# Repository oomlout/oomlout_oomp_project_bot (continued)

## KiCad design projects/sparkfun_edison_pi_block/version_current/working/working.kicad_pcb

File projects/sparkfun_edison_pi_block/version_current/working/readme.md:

# OOMP Project  
## Edison_Pi_Block  by sparkfun  
  
oomp key: oomp_projects_flat_sparkfun_edison_pi_block  
(snippet of original readme)  
  
SparkFun Edison Pi Block  
========================  

[*SparkFun Edison Pi Block (DEV-13044)*](https://www.sparkfun.com/products/13044)  
  
The Pi Block is a simple breakout board to bring the GPIO from the Intel Edison to the user. The Block provides level-shifted access to basic GPIO, PWM, UART, I<sup>2</sup>C, and SPI. The pins are presented in the same configuration as a [Raspberry Pi Model B header](http://elinux.org/RPi_Low-level_peripherals-Model_A_and_B_.28Original.29).  
  
Access to the GPIO pins can be accomplished through [MRAA](https://github.com/intel-iot-devkit/mraa). The GPIO number listed on the board or Linux is not the same as MRAA. Refer to the table to see which GPIO pin maps to which number in MRAA.   
  
*MRAA pin map table based on [Intel's IOT Dev Kit Repository](https://github.com/intel-iot-devkit/mraa/blob/master/docs/edison.md)*  
  
*Pins on the Pi Block are denoted with a * after the GP number*  
  
<table class="table table-bordered">  
<thead><tr><th class="text-center" title="Field -1">Edison Pin (Linux)</th>  
<th class="text-center" title="Field -2">Arduino Breakout</th>  
<th class="text-center" title="Field -3">Mini Breakout</th>  
<th class="text-center" title="Field -4">MRAA Number</th>  
<th class="text-center" title="Field -5">Pinmode0</th>  
<th class="text-center" title="Field -6">Pinmode1</th>  
<th class="text-center" title="Field -7">Pinmode2</th>  
</tr></thead>  
<tbody><tr cla  
  full source readme at [readme_src.md](readme_src.md)  
  
source repo at: [https://github.com/sparkfun/Edison_Pi_Block](https://github.com/sparkfun/Edison_Pi_Block)  
## Board  

## Schematic  

[schematic pdf](working_schematic.pdf)  
## Images

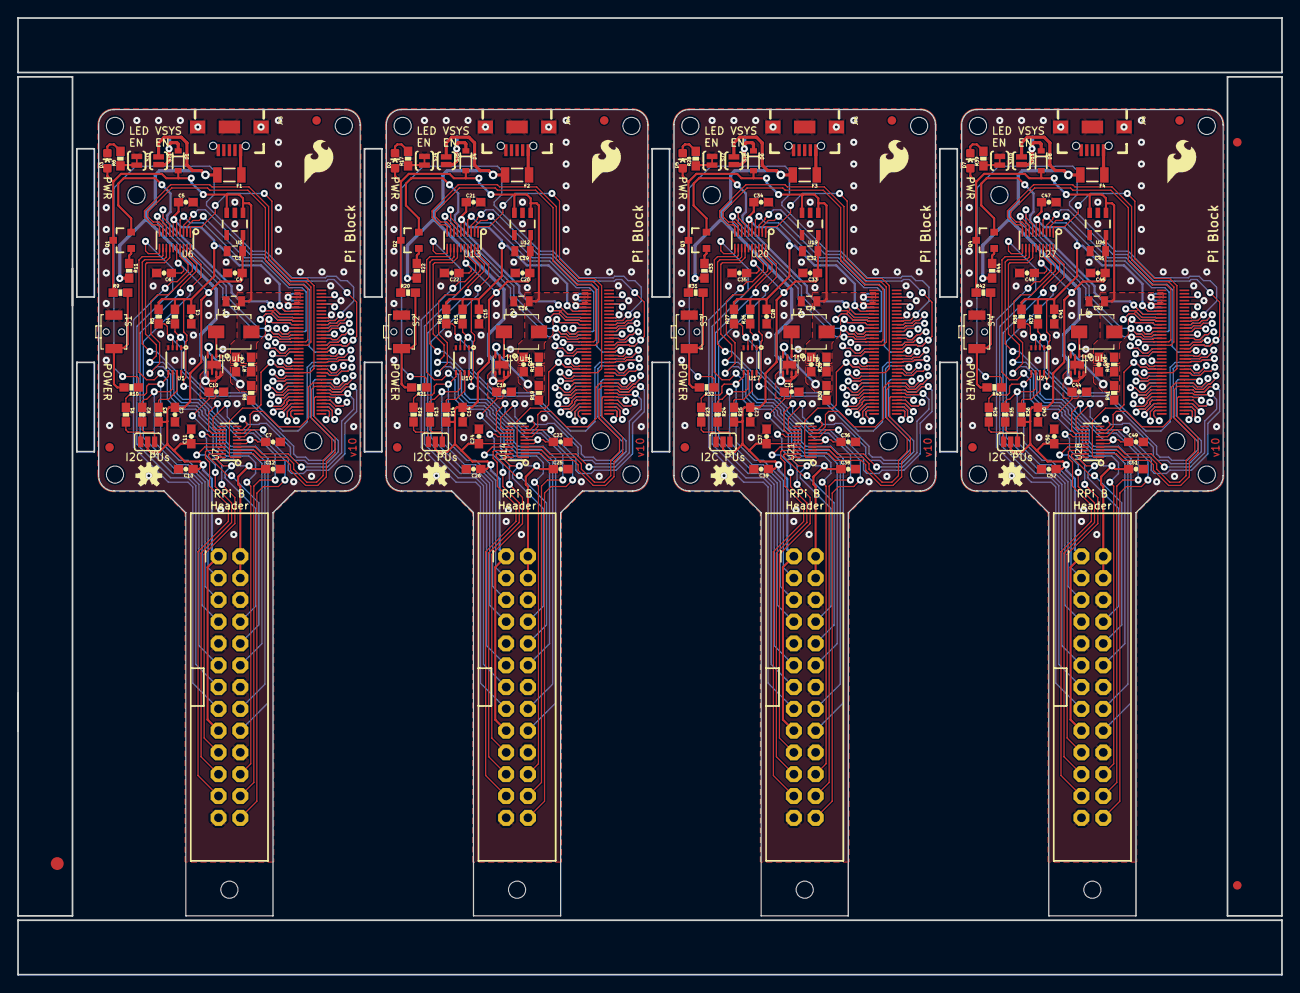
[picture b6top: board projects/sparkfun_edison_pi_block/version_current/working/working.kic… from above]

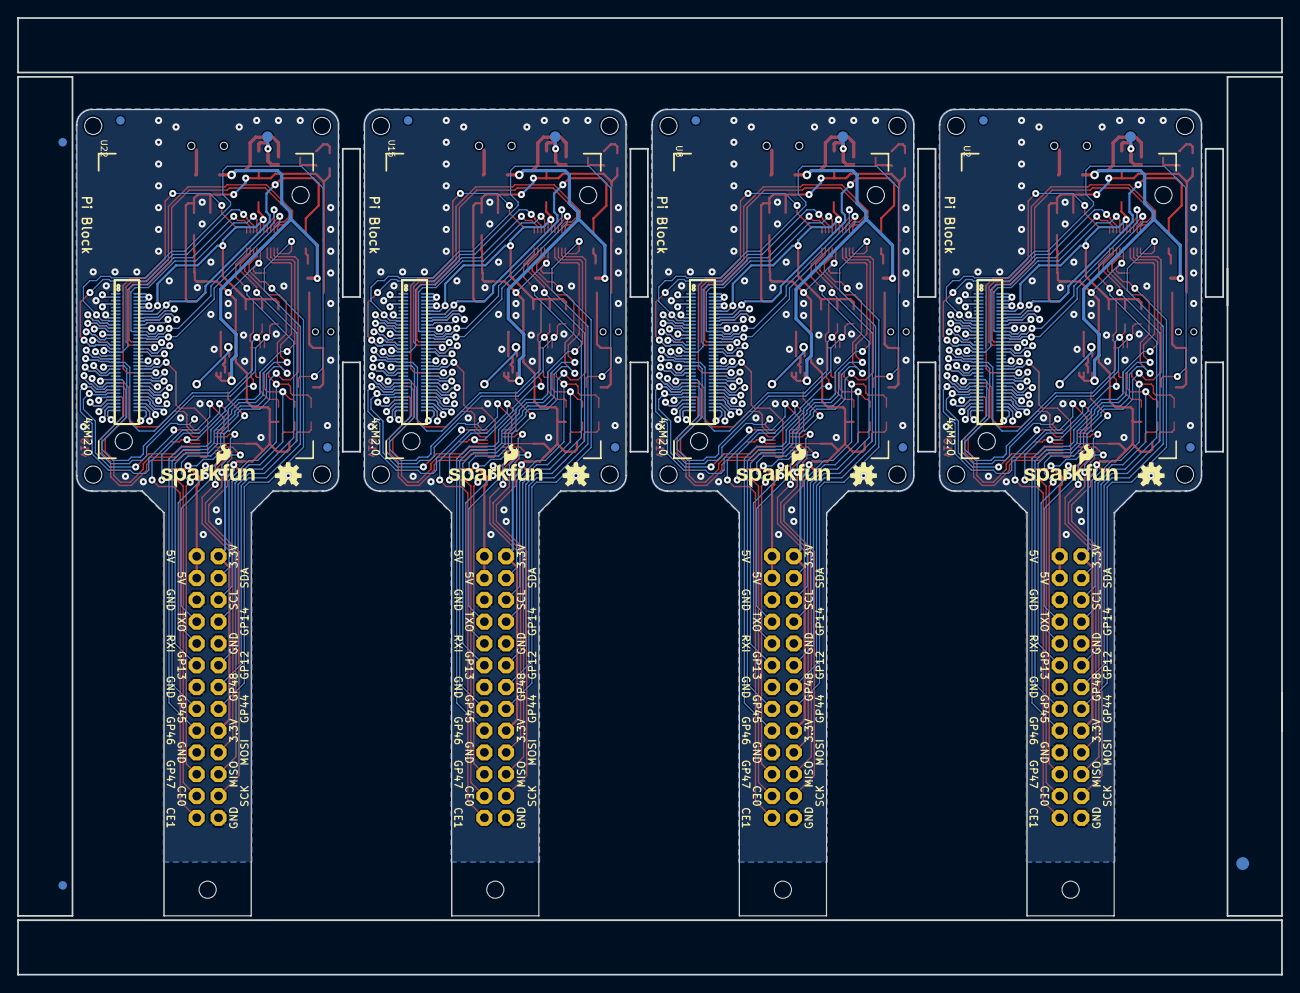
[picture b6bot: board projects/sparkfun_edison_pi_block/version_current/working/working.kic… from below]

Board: 4 copper layers, 147.3 x 111.5 mm, 230 parts (31 on the bottom side), 352 nets.

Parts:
@HOLE0, @HOLE1, @HOLE2, @HOLE3, @HOLE4, @HOLE5, @HOLE6, @HOLE7, @HOLE8, @HOLE9, @HOLE10, @HOLE11, @HOLE12, @HOLE13, @HOLE14, @HOLE15, @HOLE16, @HOLE17, @HOLE18, @HOLE19: (no value)
C1, C2, C4, C5, C6, C7, C11, C14, C15, C20, C21, C22, C23, C24, C27, C28, C33, C34, C35, C36, C37, C40, C41, C46, C47, C48, C49, C50: 0.1uF; 0603-CAP
C3, C19, C32, C45: 10uF; 0805
C8, C16, C29, C42: 22uF; 0805
C9, C17, C30, C43: 9.0pF; 0603-CAP
C10, C18, C31, C44: 4.7uF; 0603-CAP
C12, C13, C25, C26, C38, C39, C51, C52: 1.0uF; 0603-CAP
D1, D4, D6, D8: BAT20J; SOD-323
D2, D3, D5, D7: BLUE; LED-0603
E$1, E$2: FIDUCIAL-1.5X3
E$3, E$4, E$5, E$6: FIDUCIAL-1X2
F1, F2, F3, F4: PTCSMD; PTC-1206
FID1, FID2, FID3, FID4, FID5, FID6, FID7, FID8, FID9, FID10, FID11, FID12, FID13, FID14, FID15, FID16: FIDUCIAL1X2; FIDUCIAL-1X2
JP1, JP2, JP5, JP7: RASPBERRYPI-GPIOPTH; 2X13-SHROUDED
JP3, JP4, JP6, JP8: USB_MICROB; USB-B-MICRO-SMD_V03
L1, L2, L3, L4: 1.0uH; INDUCTOR-SRP4020
LOGO1, LOGO2, LOGO5, LOGO6, LOGO9, LOGO10, LOGO13, LOGO14: OSHW-LOGOS; OSHW-LOGO-S
LOGO3, LOGO8, LOGO12, LOGO16: SFE_LOGO_FLAME.2_INCH; SFE_LOGO_FLAME_.2
LOGO4, LOGO7, LOGO11, LOGO15: SFE_LOGO_NAME_FLAME.1_INCH; SFE_LOGO_NAME_FLAME_.1
Q1, Q2, Q3, Q4: 200mA/50V; SOT23-3
R1, R2, R9, R12, R13, R20, R23, R24, R31, R34, R35, R42: 10K; 0603-RES
R3, R14, R25, R36: 200k; 0603-RES
R4, R5, R15, R16, R26, R27, R37, R38: DNP; 0603-RES
R6, R11, R17, R22, R28, R33, R39, R44: 1K; 0603-RES
R7, R18, R29, R40: 680k; 0603-RES
R8, R19, R30, R41: 120k; 0603-RES
R10, R21, R32, R43: 220; 0603-RES
S1, S2, S3, S4: POWER; TACTILE_SWITCH-SMD-RIGHT-ANGLE
SJ1, SJ5, SJ8, SJ11: JUMPER-PAD-2-NOYES_SILK; PAD-JUMPER-2-NO_YES_SILK
SJ2, SJ6, SJ9, SJ12: JUMPER-PAD-3-NC_BY_PASTE; PAD-JUMPER-3-NC_BY_PASTE_YES_SILK_FULL_BOX
SJ3, SJ4, SJ7, SJ10: JUMPER-PAD-2-NC_BY_TRACE; PAD-JUMPER-2-NC_BY_TRACE_YES_SILK
TP1, TP2, TP3, TP4: TEST-POINT3X5; PAD.03X.05
U1, U10, U17, U24: PCA9306; PCA9306DC-1_1
U2, U8, U15, U22: EDISON_CONNECTOR_FULLMOUNTING_HOLES; EDISON_DAUGHTER
U3, U9, U16, U23: EDISON_CONNECTOR_FULLHEADER; DF40C-70DP-0.4(51)
U4, U11, U18, U25: TPS62065; WSON-8-PAD
U5, U12, U19, U26: MIC5219 3.3V; SOT23-5
U6, U7, U13, U14, U20, U21, U27, U28: TXB0108; UFDFN-20

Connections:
1.8V: C1.1, C5.1, C7.1, R4.2, R5.2, U1.1, U2.12, U3.12, U6.5, U6.6, U7.5, U7.6
1.8V1: C15.1, C21.1, C23.1, R15.2, R16.2, U8.12, U9.12, U10.1, U13.5, U13.6, U14.5, U14.6
1.8V2: C28.1, C34.1, C36.1, R26.2, R27.2, U15.12, U16.12, U17.1, U20.5, U20.6, U21.5, U21.6
1.8V3: C41.1, C47.1, C49.1, R37.2, R38.2, U22.12, U23.12, U24.1, U27.5, U27.6, U28.5, U28.6
3.3V: U2.8, U2.10, U3.8, U3.10
3.3V1: U8.8, U8.10, U9.8, U9.10
3.3V2: U15.8, U15.10, U16.8, U16.10
3.3V3: U22.8, U22.10, U23.8, U23.10
3.3V_LOCAL: C2.1, C3.1, C4.1, C6.1, C11.1, C13.1, JP1.1, JP1.17, R3.2, SJ2.2, U5.5, U6.16, U7.16
3.3V_LOCAL1: C14.1, C19.1, C20.1, C22.1, C24.1, C26.1, JP2.1, JP2.17, R14.2, SJ6.2, U12.5, U13.16, U14.16
3.3V_LOCAL2: C27.1, C32.1, C33.1, C35.1, C37.1, C39.1, JP5.1, JP5.17, R25.2, SJ9.2, U19.5, U20.16, U21.16
3.3V_LOCAL3: C40.1, C45.1, C46.1, C48.1, C50.1, C52.1, JP7.1, JP7.17, R36.2, SJ12.2, U26.5, U27.16, U28.16
5V: C10.1, C12.1, F1.2, JP1.2, JP1.4, R11.2, SJ1.1, U4.5, U4.7, U4.8
5V1: C18.1, C25.1, F2.2, JP2.2, JP2.4, R22.2, SJ5.1, U11.5, U11.7, U11.8
5V2: C31.1, C38.1, F3.2, JP5.2, JP5.4, R33.2, SJ8.1, U18.5, U18.7, U18.8
5V3: C44.1, C51.1, F4.2, JP7.2, JP7.4, R44.2, SJ11.1, U25.5, U25.7, U25.8
DCIN: Q1.2, U2.14, U3.14
DCIN1: Q2.2, U8.14, U9.14
DCIN2: Q3.2, U15.14, U16.14
DCIN3: Q4.2, U22.14, U23.14
FAULT: U2.19, U3.19
FAULT1: U8.19, U9.19
FAULT2: U15.19, U16.19
FAULT3: U22.19, U23.19
FW_RCVR: U2.69, U3.69
FW_RCVR1: U8.69, U9.69
FW_RCVR2: U15.69, U16.69
FW_RCVR3: U22.69, U23.69
GND: C1.2, C2.2, C3.2, C4.2, C5.2, C6.2, C7.2, C8.2, C10.2, C11.2, C12.2, C13.2, JP1.6, JP1.9, JP1.14, JP1.20, JP1.25, JP3.GND1, JP3.SHIELD1, JP3.SHIELD2, JP3.SHIELD3, R8.1, S1.1, SJ3.1, U1.4, U2.1, U2.5, U2.9, U2.11, U2.13, U2.15, U3.1, U3.5, U3.9, U3.11, U3.13, U3.15, U4.1, U4.3, U4.6, U4.PAD, U5.2, U6.15, U7.15
GND1: C14.2, C15.2, C16.2, C18.2, C19.2, C20.2, C21.2, C22.2, C23.2, C24.2, C25.2, C26.2, JP2.6, JP2.9, JP2.14, JP2.20, JP2.25, JP4.GND1, JP4.SHIELD1, JP4.SHIELD2, JP4.SHIELD3, R19.1, S2.1, SJ4.1, U8.1, U8.5, U8.9, U8.11, U8.13, U8.15, U9.1, U9.5, U9.9, U9.11, U9.13, U9.15, U10.4, U11.1, U11.3, U11.6, U11.PAD, U12.2, U13.15, U14.15
GND2: C27.2, C28.2, C29.2, C31.2, C32.2, C33.2, C34.2, C35.2, C36.2, C37.2, C38.2, C39.2, JP5.6, JP5.9, JP5.14, JP5.20, JP5.25, JP6.GND1, JP6.SHIELD1, JP6.SHIELD2, JP6.SHIELD3, R30.1, S3.1, SJ7.1, U15.1, U15.5, U15.9, U15.11, U15.13, U15.15, U16.1, U16.5, U16.9, U16.11, U16.13, U16.15, U17.4, U18.1, U18.3, U18.6, U18.PAD, U19.2, U20.15, U21.15
GND3: C40.2, C41.2, C42.2, C44.2, C45.2, C46.2, C47.2, C48.2, C49.2, C50.2, C51.2, C52.2, JP7.6, JP7.9, JP7.14, JP7.20, JP7.25, JP8.GND1, JP8.SHIELD1, JP8.SHIELD2, JP8.SHIELD3, R41.1, S4.1, SJ10.1, U22.1, U22.5, U22.9, U22.11, U22.13, U22.15, U23.1, U23.5, U23.9, U23.11, U23.13, U23.15, U24.4, U25.1, U25.3, U25.6, U25.PAD, U26.2, U27.15, U28.15
GP1: U8.48, U9.48, U13.1
GP2: U8.42, U9.42
GP3: U8.34, U9.34
GP4: U8.32, U9.32, U13.10
GP5: U8.30, U9.30, U13.9
GP6: U8.28, U9.28, U13.8
GP7: U8.26, U9.26, U13.7
GP8: U8.25, U9.25
GP9: U8.24, U9.24, U13.4
GP10: U15.48, U16.48, U20.1
GP11: U15.42, U16.42
GP12: U15.34, U16.34
GP12_PWM0: U2.35, U3.35, U6.2
GP12_PWM1: U8.35, U9.35, U13.2
GP12_PWM2: U15.35, U16.35, U20.2
GP12_PWM3: U22.35, U23.35, U27.2
GP13: U15.32, U16.32, U20.10
GP13_PWM1: U2.33, U3.33, U6.3
GP13_PWM2: U8.33, U9.33, U13.3
GP13_PWM3: U15.33, U16.33, U20.3
GP13_PWM4: U22.33, U23.33, U27.3
GP14: U2.48, U3.48, U6.1
GP15: U2.42, U3.42
GP16: U15.30, U16.30, U20.9
GP17: U15.28, U16.28, U20.8
GP18: U15.26, U16.26, U20.7
GP19: U15.25, U16.25
GP19_I2C_1_SCL: R4.1, U1.2, U2.41, U3.41
GP19_I2C_1_SCL1: R15.1, U8.41, U9.41, U10.2
GP19_I2C_1_SCL2: R26.1, U15.41, U16.41, U17.2
GP19_I2C_1_SCL3: R37.1, U22.41, U23.41, U24.2
GP20: U15.24, U16.24, U20.4
GP20_I2C_1_SDA: R5.1, U1.3, U2.43, U3.43
GP20_I2C_1_SDA1: R16.1, U8.43, U9.43, U10.3
GP20_I2C_1_SDA2: R27.1, U15.43, U16.43, U17.3
GP20_I2C_1_SDA3: R38.1, U22.43, U23.43, U24.3
GP21: U22.48, U23.48, U27.1
GP22: U22.42, U23.42
GP23: U22.34, U23.34
GP24: U22.32, U23.32, U27.10
GP25: U22.30, U23.30, U27.9
GP26: U22.28, U23.28, U27.8
GP27: U22.26, U23.26, U27.7
GP27_I2C_6_SCL: U2.45, U3.45
GP27_I2C_6_SCL1: U8.45, U9.45
GP27_I2C_6_SCL2: U15.45, U16.45
GP27_I2C_6_SCL3: U22.45, U23.45
GP28: U22.25, U23.25
GP28_I2C_6_SDA: U2.47, U3.47
GP28_I2C_6_SDA1: U8.47, U9.47
GP28_I2C_6_SDA2: U15.47, U16.47
GP28_I2C_6_SDA3: U22.47, U23.47
GP29: U22.24, U23.24, U27.4
GP40_I2S_2_CLK: U2.52, U3.52
GP40_I2S_2_CLK1: U8.52, U9.52
GP40_I2S_2_CLK2: U15.52, U16.52
GP40_I2S_2_CLK3: U22.52, U23.52
GP41_I2S_2_FS: U2.54, U3.54
GP41_I2S_2_FS1: U8.54, U9.54
GP41_I2S_2_FS2: U15.54, U16.54
GP41_I2S_2_FS3: U22.54, U23.54
GP42_I2S_2_RXD: U2.50, U3.50
GP42_I2S_2_RXD1: U8.50, U9.50
GP42_I2S_2_RXD2: U15.50, U16.50
GP42_I2S_2_RXD3: U22.50, U23.50
GP43_I2S_2_TXD: U2.56, U3.56
GP43_I2S_2_TXD1: U8.56, U9.56
GP43_I2S_2_TXD2: U15.56, U16.56
GP43_I2S_2_TXD3: U22.56, U23.56
GP44: U2.24, U3.24, U6.4
GP45: U2.26, U3.26, U6.7
GP46: U2.28, U3.28, U6.8
GP47: U2.30, U3.30, U6.9
GP48: U2.32, U3.32, U6.10
GP49: U2.34, U3.34
GP77_SD_0_CD#: U2.60, U3.60
GP77_SD_0_CD#1: U8.60, U9.60
GP77_SD_0_CD#2: U15.60, U16.60
GP77_SD_0_CD#3: U22.60, U23.60
GP78_SD_0_CLK: U2.58, U3.58
GP78_SD_0_CLK1: U8.58, U9.58
GP78_SD_0_CLK2: U15.58, U16.58
GP78_SD_0_CLK3: U22.58, U23.58
GP79_SD_0_CMD: U2.62, U3.62
GP79_SD_0_CMD1: U8.62, U9.62
GP79_SD_0_CMD2: U15.62, U16.62
GP79_SD_0_CMD3: U22.62, U23.62
GP80_SD_0_DAT0: U2.66, U3.66
GP80_SD_0_DAT1: U8.66, U9.66
GP80_SD_0_DAT2: U15.66, U16.66
GP80_SD_0_DAT3: U22.66, U23.66
GP81_SD_0_DAT1: U2.70, U3.70
GP81_SD_0_DAT2: U8.70, U9.70
GP81_SD_0_DAT3: U15.70, U16.70
GP81_SD_0_DAT4: U22.70, U23.70
GP82_SD_0_DAT1: U8.64, U9.64
GP82_SD_0_DAT2: U2.64, U3.64
GP82_SD_0_DAT3: U15.64, U16.64
GP82_SD_0_DAT4: U22.64, U23.64
GP83_SD_0_DAT1: U8.68, U9.68
GP83_SD_0_DAT2: U15.68, U16.68
GP83_SD_0_DAT3: U2.68, U3.68
GP83_SD_0_DAT4: U22.68, U23.68
GP84_SD_CLK_FB: U2.44, U3.44
GP84_SD_CLK_FB1: U8.44, U9.44
GP84_SD_CLK_FB2: U15.44, U16.44
GP84_SD_CLK_FB3: U22.44, U23.44
GP109_SPI_2_CLK: U2.55, U3.55, U7.3
GP109_SPI_2_CLK1: U8.55, U9.55, U14.3
GP109_SPI_2_CLK2: U15.55, U16.55, U21.3
GP109_SPI_2_CLK3: U22.55, U23.55, U28.3
GP110_SPI_2_FS0: U2.53, U3.53, U7.8
GP110_SPI_2_FS1: U8.53, U9.53, U14.8
GP110_SPI_2_FS2: U15.53, U16.53, U21.8
GP110_SPI_2_FS3: U22.53, U23.53, U28.8
GP111_SPI_2_FS1: U2.51, U3.51, U7.9
GP111_SPI_2_FS2: U8.51, U9.51, U14.9
GP111_SPI_2_FS3: U15.51, U16.51, U21.9
GP111_SPI_2_FS4: U22.51, U23.51, U28.9
GP114_SPI_2_RXD: U2.59, U3.59, U7.4
GP114_SPI_2_RXD1: U8.59, U9.59, U14.4
GP114_SPI_2_RXD2: U15.59, U16.59, U21.4
GP114_SPI_2_RXD3: U22.59, U23.59, U28.4
GP115_SPI_2_TXD: U2.57, U3.57, U7.7
GP115_SPI_2_TXD1: U8.57, U9.57, U14.7
GP115_SPI_2_TXD2: U15.57, U16.57, U21.7
GP115_SPI_2_TXD3: U22.57, U23.57, U28.7
GP128_UART_1_CTS: U2.65, U3.65
GP128_UART_1_CTS1: U8.65, U9.65
GP128_UART_1_CTS2: U15.65, U16.65
GP128_UART_1_CTS3: U22.65, U23.65
GP129_UART_1_RTS: U2.63, U3.63
GP129_UART_1_RTS1: U8.63, U9.63
GP129_UART_1_RTS2: U15.63, U16.63
GP129_UART_1_RTS3: U22.63, U23.63
GP130_UART_1_RX: U2.61, U3.61, U7.2
GP130_UART_1_RX1: U8.61, U9.61, U14.2
GP130_UART_1_RX2: U15.61, U16.61, U21.2
GP130_UART_1_RX3: U22.61, U23.61, U28.2
GP131_UART_1_TX: U2.46, U3.46, U7.1
GP131_UART_1_TX1: U8.46, U9.46, U14.1
GP131_UART_1_TX2: U15.46, U16.46, U21.1
GP131_UART_1_TX3: U22.46, U23.46, U28.1
GP134_UART_2_RX: U2.22, U3.22
GP134_UART_2_RX1: U8.22, U9.22
GP134_UART_2_RX2: U15.22, U16.22
GP134_UART_2_RX3: U22.22, U23.22
GP135_UART_2_TX: U2.27, U3.27
GP135_UART_2_TX1: U8.27, U9.27
GP135_UART_2_TX2: U15.27, U16.27
GP135_UART_2_TX3: U22.27, U23.27
GP165: U2.25, U3.25
GP182_PWM1: U8.37, U9.37
GP182_PWM2: U2.37, U3.37
GP182_PWM3: U15.37, U16.37
GP182_PWM4: U22.37, U23.37
GP183_PWM1: U8.39, U9.39
GP183_PWM2: U15.39, U16.39
GP183_PWM3: U2.39, U3.39
GP183_PWM4: U22.39, U23.39
HV_SCL: JP1.5, R2.1, U1.6
HV_SCL1: JP2.5, R13.1, U10.6
HV_SCL2: JP5.5, R24.1, U17.6
HV_SCL3: JP7.5, R35.1, U24.6
HV_SDA: JP1.3, R1.1, U1.5
HV_SDA1: JP2.3, R12.1, U10.5
HV_SDA2: JP5.3, R23.1, U17.5
HV_SDA3: JP7.3, R34.1, U24.5
MSIC_SLP_CLK: U2.7, U3.7
MSIC_SLP_CLK1: U8.7, U9.7
MSIC_SLP_CLK2: U15.7, U16.7
MSIC_SLP_CLK3: U22.7, U23.7
unnamed: R3.1, U1.7, U1.8
unnamed: F1.1, JP3.VBUS1
unnamed: D1.C, SJ1.2, TP1.P$1
unnamed: R1.2, SJ2.3
unnamed: R2.2, SJ2.1
unnamed: R14.1, U10.7, U10.8
unnamed: F2.1, JP4.VBUS1
unnamed: D2.C, R17.2
unnamed: R17.1, SJ4.2
unnamed: C17.2, R18.1, R19.2, U11.4
unnamed: L2.P$1, U11.2
unnamed: D3.C, R6.2
unnamed: R6.1, SJ3.2
unnamed: R20.2, R21.2, S2.2
unnamed: R9.2, R10.2, S1.2
unnamed: Q1.1, R11.1
unnamed: Q2.1, R22.1
unnamed: C9.2, R7.1, R8.2, U4.4
unnamed: L1.P$1, U4.2
unnamed: D4.C, SJ5.2, TP2.P$1
unnamed: R12.2, SJ6.3
unnamed: R13.2, SJ6.1
unnamed: R25.1, U17.7, U17.8
unnamed: F3.1, JP6.VBUS1
unnamed: D5.C, R28.2
unnamed: R28.1, SJ7.2
unnamed: C30.2, R29.1, R30.2, U18.4
unnamed: L3.P$1, U18.2
unnamed: R31.2, R32.2, S3.2
unnamed: Q3.1, R33.1
unnamed: D6.C, SJ8.2, TP3.P$1
unnamed: R23.2, SJ9.3
unnamed: R24.2, SJ9.1
unnamed: R36.1, U24.7, U24.8
unnamed: F4.1, JP8.VBUS1
unnamed: D7.C, R39.2
unnamed: R39.1, SJ10.2
unnamed: C43.2, R40.1, R41.2, U25.4
unnamed: L4.P$1, U25.2
unnamed: R42.2, R43.2, S4.2
unnamed: Q4.1, R44.1
unnamed: D8.C, SJ11.2, TP4.P$1
unnamed: R34.2, SJ12.3
unnamed: R35.2, SJ12.1
OSC_CLK_OUT: U2.67, U3.67
OSC_CLK_OUT1: U8.67, U9.67
OSC_CLK_OUT2: U15.67, U16.67
OSC_CLK_OUT3: U22.67, U23.67
PI_CE0: JP1.24, U7.13
PI_CE1: JP1.26, U7.12
PI_CE2: JP2.24, U14.13
PI_CE3: JP2.26, U14.12
PI_CE4: JP5.24, U21.13
PI_CE5: JP5.26, U21.12
PI_CE6: JP7.24, U28.13
PI_CE7: JP7.26, U28.12
PI_GP1: JP2.7, U13.20
PI_GP2: JP2.11, U13.19
PI_GP3: JP2.15, U13.17
PI_GP4: JP1.7, U6.20
PI_GP5: JP2.16, U13.14
PI_GP6: JP2.18, U13.13
PI_GP7: JP2.22, U13.12
PI_GP8: JP2.13, U13.11
PI_GP9: JP5.7, U20.20
PI_GP10: JP5.11, U20.19
PI_GP11: JP5.15, U20.17
PI_GP12: JP5.16, U20.14
PI_GP13: JP5.18, U20.13
PI_GP14: JP5.22, U20.12
PI_GP15: JP5.13, U20.11
PI_GP16: JP7.7, U27.20
PI_GP17: JP1.11, U6.19
PI_GP18: JP7.11, U27.19
PI_GP18#: JP1.12, U6.18
PI_GP18#1: JP2.12, U13.18
PI_GP18#2: JP5.12, U20.18
PI_GP18#3: JP7.12, U27.18
PI_GP19: JP7.15, U27.17
PI_GP20: JP7.16, U27.14
PI_GP21: JP7.18, U27.13
PI_GP22: JP1.15, U6.17
PI_GP23: JP1.16, U6.14
PI_GP24: JP1.18, U6.13
PI_GP25: JP1.22, U6.12
PI_GP26: JP7.22, U27.12
PI_GP27: JP1.13, U6.11
PI_GP28: JP7.13, U27.11
PI_MISO: JP1.21, U7.17
PI_MISO1: JP2.21, U14.17
PI_MISO2: JP5.21, U21.17
PI_MISO3: JP7.21, U28.17
PI_MOSI: JP1.19, U7.14
PI_MOSI1: JP2.19, U14.14
PI_MOSI2: JP5.19, U21.14
PI_MOSI3: JP7.19, U28.14
PI_RXI: JP1.10, U7.19
PI_RXI1: JP2.10, U14.19
PI_RXI2: JP5.10, U21.19
PI_RXI3: JP7.10, U28.19
PI_SCLK: JP1.23, U7.18
PI_SCLK1: JP2.23, U14.18
PI_SCLK2: JP5.23, U21.18
PI_SCLK3: JP7.23, U28.18
PI_TXO: JP1.8, U7.20
PI_TXO1: JP2.8, U14.20
PI_TXO2: JP5.8, U21.20
PI_TXO3: JP7.8, U28.20
PSW: U2.21, U3.21
PSW1: U8.21, U9.21
PSW2: U15.21, U16.21
PSW3: U22.21, U23.21
PWRBTN#: R10.1, U2.17, U3.17
PWRBTN#1: R21.1, U8.17, U9.17
PWRBTN#2: R32.1, U15.17, U16.17
PWRBTN#3: R43.1, U22.17, U23.17
RCVR_MODE: U2.31, U3.31
RCVR_MODE1: U8.31, U9.31
RCVR_MODE2: U15.31, U16.31
RCVR_MODE3: U22.31, U23.31
RESET_OUT#: U2.36, U3.36
RESET_OUT#1: U8.36, U9.36
RESET_OUT#2: U15.36, U16.36
RESET_OUT#3: U22.36, U23.36
USB_DN: U2.18, U3.18
USB_DN1: U8.18, U9.18
USB_DN2: U15.18, U16.18
USB_DN3: U22.18, U23.18
USB_DP: U2.16, U3.16
USB_DP1: U8.16, U9.16
USB_DP2: U15.16, U16.16
USB_DP3: U22.16, U23.16
USB_ID: U2.3, U3.3
USB_ID1: U8.3, U9.3
USB_ID2: U15.3, U16.3
USB_ID3: U22.3, U23.3
USB_VBUS: U2.20, U3.20
USB_VBUS1: U8.20, U9.20
USB_VBUS2: U15.20, U16.20
USB_VBUS3: U22.20, U23.20
VSYS: C8.1, C9.1, D1.A, D3.A, L1.P$2, Q1.3, R7.2, R9.1, U2.2, U2.4, U2.6, U3.2, U3.4, U3.6, U5.1, U5.3
VSYS1: C16.1, C17.1, D2.A, D4.A, L2.P$2, Q2.3, R18.2, R20.1, U8.2, U8.4, U8.6, U9.2, U9.4, U9.6, U12.1, U12.3
VSYS2: C29.1, C30.1, D5.A, D6.A, L3.P$2, Q3.3, R29.2, R31.1, U15.2, U15.4, U15.6, U16.2, U16.4, U16.6, U19.1, U19.3
VSYS3: C42.1, C43.1, D7.A, D8.A, L4.P$2, Q4.3, R40.2, R42.1, U22.2, U22.4, U22.6, U23.2, U23.4, U23.6, U26.1, U26.3
V_BAT_BKUP: U2.23, U3.23
V_BAT_BKUP1: U8.23, U9.23
V_BAT_BKUP2: U15.23, U16.23
V_BAT_BKUP3: U22.23, U23.23

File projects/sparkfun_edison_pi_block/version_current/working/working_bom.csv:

"Id";"Designator";"Footprint";"Quantity";"Designation";"Supplier and ref";
1;"SJ12,SJ2,SJ6,SJ9";"PAD-JUMPER-3-NC_BY_PASTE_YES_SILK_FULL_BOX";4;"JUMPER-PAD-3-NC_BY_PASTE";;;
2;"R5,R26,R16,R27,R38,R37,R4,R15";"0603-RES";8;"DNP";;;
3;"U28,U20,U21,U6,U27,U14,U7,U13";"UFDFN-20";8;"TXB0108";;;
4;"R7,R18,R29,R40";"0603-RES";4;"680k";;;
5;"C15,C6,C27,C4,C49,C34,C41,C36,C40,C46,C37,C28,C48,C24,C14,C1,C2,C5,C33,C21,C47,C22,C20,C23,C7,C35,C11,C50";"0603-CAP";28;"0.1uF";;;
6;"R42,R24,R9,R23,R1,R31,R12,R13,R20,R2,R35,R34";"0603-RES";12;"10K";;;
7;"SJ10,SJ3,SJ4,SJ7";"PAD-JUMPER-2-NC_BY_TRACE_YES_SILK";4;"JUMPER-PAD-2-NC_BY_TRACE";;;
8;"LOGO16,LOGO8,LOGO3,LOGO12";"SFE_LOGO_FLAME_.2";4;"SFE_LOGO_FLAME.2_INCH";;;
9;"C44,C31,C10,C18";"0603-CAP";4;"4.7uF";;;
10;"C52,C26,C13,C39,C12,C25,C51,C38";"0603-CAP";8;"1.0uF";;;
11;"@HOLE12,@HOLE3,@HOLE2,@HOLE11,@HOLE6,@HOLE5,@HOLE1,@HOLE13,@HOLE0,@HOLE15,@HOLE10,@HOLE8,@HOLE16,@HOLE18,@HOLE19,@HOLE14,@HOLE7,@HOLE4,@HOLE17,@HOLE9";"";20;"";;;
12;"JP1,JP5,JP7,JP2";"2X13-SHROUDED";4;"RASPBERRYPI-GPIOPTH";;;
13;"R10,R21,R32,R43";"0603-RES";4;"220";;;
14;"L1,L3,L2,L4";"INDUCTOR-SRP4020";4;"1.0uH";;;
15;"R28,R33,R39,R44,R11,R6,R22,R17";"0603-RES";8;"1K";;;
16;"FID10,FID5,FID14,FID2,FID9,FID13,FID1,FID6,FID7,FID12,FID15,FID4,FID11,FID16,FID8,FID3";"FIDUCIAL-1X2";16;"FIDUCIAL1X2";;;
17;"U1,U24,U10,U17";"PCA9306DC-1_1";4;"PCA9306";;;
18;"D4,D6,D1,D8";"SOD-323";4;"BAT20J";;;
19;"C43,C30,C9,C17";"0603-CAP";4;"9.0pF";;;
20;"D7,D2,D3,D5";"LED-0603";4;"BLUE";;;
21;"U11,U25,U18,U4";"WSON-8-PAD";4;"TPS62065";;;
22;"C19,C32,C3,C45";"0805";4;"10uF";;;
23;"R25,R14,R36,R3";"0603-RES";4;"200k";;;
24;"JP8,JP6,JP4,JP3";"USB-B-MICRO-SMD_V03";4;"USB_MICROB";;;
25;"U5,U19,U26,U12";"SOT23-5";4;"MIC5219 3.3V";;;
26;"Q1,Q2,Q3,Q4";"SOT23-3";4;"200mA/50V";;;
27;"C8,C16,C29,C42";"0805";4;"22uF";;;
28;"R41,R19,R30,R8";"0603-RES";4;"120k";;;
29;"E$5,E$4,E$3,E$6";"FIDUCIAL-1X2";4;"";;;
30;"F3,F2,F4,F1";"PTC-1206";4;"PTCSMD";;;
31;"LOGO10,LOGO14,LOGO6,LOGO1,LOGO9,LOGO2,LOGO5,LOGO13";"OSHW-LOGO-S";8;"OSHW-LOGOS";;;
32;"SJ8,SJ1,SJ5,SJ11";"PAD-JUMPER-2-NO_YES_SILK";4;"JUMPER-PAD-2-NOYES_SILK";;;
33;"S3,S1,S4,S2";"TACTILE_SWITCH-SMD-RIGHT-ANGLE";4;"POWER";;;
34;"E$1,E$2";"FIDUCIAL-1.5X3";2;"";;;
35;"U22,U15,U8,U2";"EDISON_DAUGHTER";4;"EDISON_CONNECTOR_FULLMOUNTING_HOLES";;;
36;"LOGO11,LOGO7,LOGO15,LOGO4";"SFE_LOGO_NAME_FLAME_.1";4;"SFE_LOGO_NAME_FLAME.1_INCH";;;
37;"TP4,TP2,TP3,TP1";"PAD.03X.05";4;"TEST-POINT3X5";;;
38;"U3,U23,U9,U16";"DF40C-70DP-0.4(51)";4;"EDISON_CONNECTOR_FULLHEADER";;;
